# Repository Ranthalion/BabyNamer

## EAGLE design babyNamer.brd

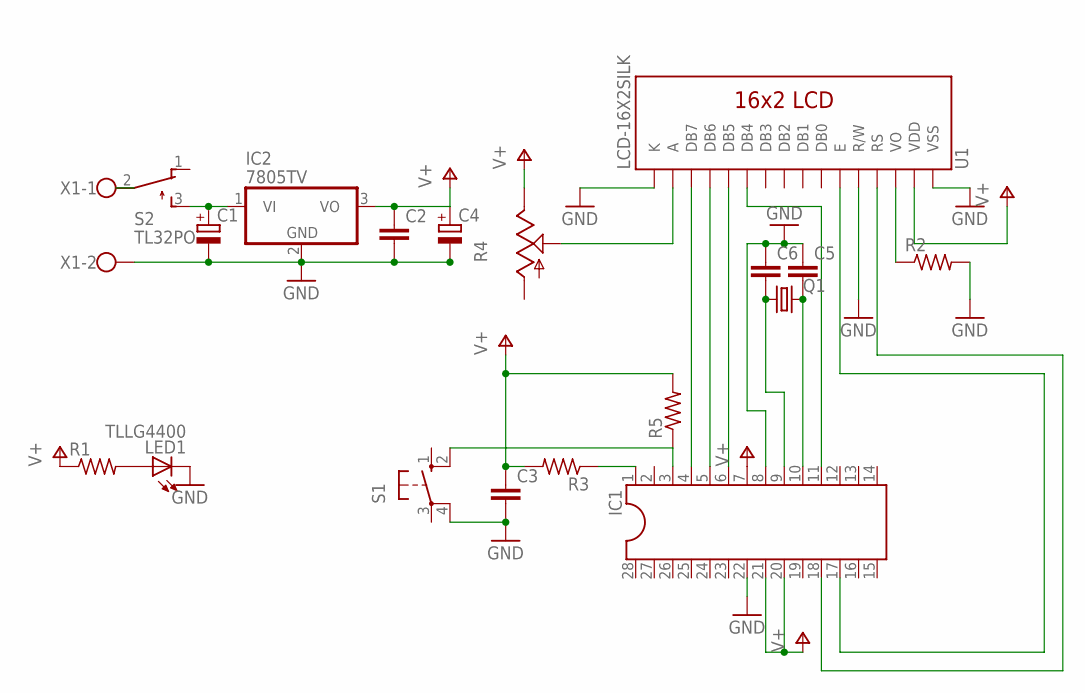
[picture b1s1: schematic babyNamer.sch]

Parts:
C1, C4: CPOL-EUE3.5-8; E3,5-8
C2, C3, C5, C6: C-EU050-024X044; C050-024X044
IC1: DIL28-3
IC2: 7805TV; TO220V
LED1: TLLG4400; LED3MM
Q1: CRYSTALHC49US; HC49US
R1, R2, R3, R5: R-US_0204/7; 0204/7
R4: TRIM_US-CA9V; CA9V
S1: 10-XX; B3F-10XX
S2: TL32PO; TL3XPO
U1: LCD-16X2SILK; LCD-16X2
X1: W237-102

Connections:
GND: C1.-, C2.2, C3.2, C4.-, C5.1, C6.1, IC1.8, IC1.22, IC2.2 (GND), LED1.K (C), R2.2, S1.4 (P1), U1.1 (VSS), U1.5 (R/W), U1.16 (K), X1.2
unnamed: IC1.17, U1.6 (E)
unnamed: R2.1, U1.3 (VO)
unnamed: IC1.11, U1.11 (DB4)
unnamed: IC1.18, U1.4 (RS)
unnamed: S2.2, X1.1
unnamed: R4.S, U1.15 (A)
unnamed: IC1.4, U1.14 (DB7)
unnamed: IC1.5, U1.13 (DB6)
unnamed: IC1.6, U1.12 (DB5)
unnamed: C1.+, IC2.1 (VI), S2.3 (S)
unnamed: LED1.A, R1.2
unnamed: C5.2, IC1.10, Q1.2
unnamed: C6.2, IC1.9, Q1.1
unnamed: IC1.1, R3.1
unnamed: IC1.3, R5.1, S1.2 (S1)
V+: C2.1, C3.1, C4.+, IC1.7, IC1.20, IC1.21, IC2.3 (VO), R1.1, R3.2, R4.E, R5.2, U1.2 (VDD)

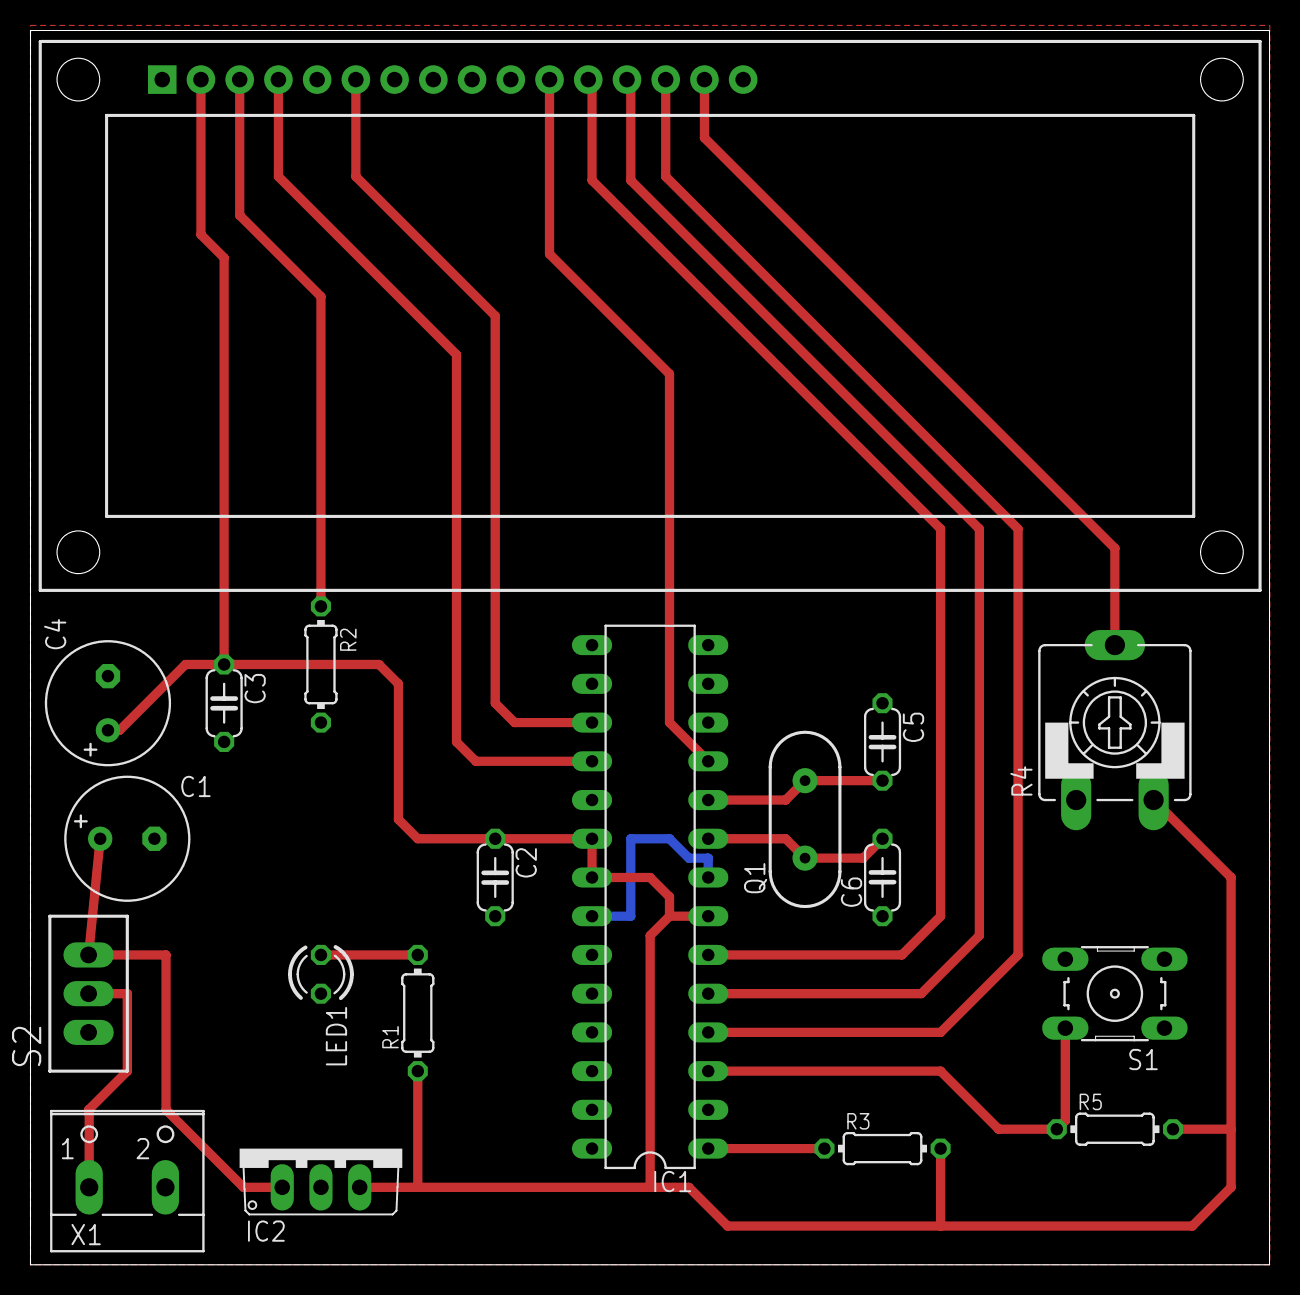
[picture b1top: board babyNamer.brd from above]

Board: 2 copper layers, 81.3 x 81.0 mm, 19 parts (0 on the bottom side), 17 nets.

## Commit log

2014-03-10 Adding to GitHub
    Baby Name code, schematics, and board
2014-06-22 Adding additional names as comments

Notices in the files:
parts and their libraries:
SparkFun-Displays: Licensing: CC v3.0 Share-Alike You are welcome to use this library for commercial purposes.
